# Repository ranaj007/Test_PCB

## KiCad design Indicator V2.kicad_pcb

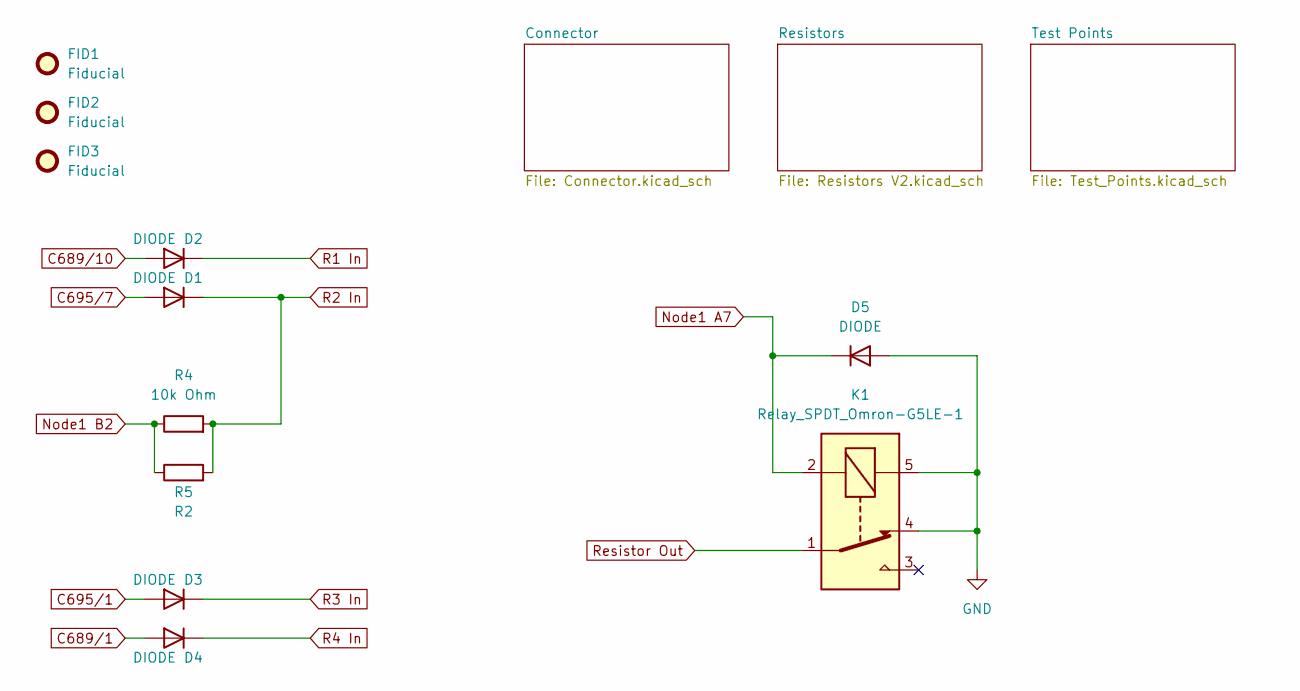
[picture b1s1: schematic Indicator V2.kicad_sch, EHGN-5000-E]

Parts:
D1, D2, D3, D4, D5: DIODE; D_SMA; MPN GS1G_R1_00001
FID1, FID2, FID3: Fiducial; Fiducial_0.5mm_Mask1.5mm
K1: Relay_SPDT_Omron-G5LE-1; MPN G5LE-14-36 DC24
R4: 10k Ohm; R_1206_3216Metric; MPN CR0805-JW-103ELF
R5: R2; R_Axial_DIN0309_L9.0mm_D3.2mm_P15.24mm_Horizontal

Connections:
C689/1: D4.2 (A); also elsewhere on the board
C689/10: D2.2 (A); also elsewhere on the board
C695/1: D3.2 (A); also elsewhere on the board
C695/7: D1.2 (A); also elsewhere on the board
GND: D5.2 (A), K1.4, K1.5; also elsewhere on the board
Node1 A7: D5.1 (K), K1.2; also elsewhere on the board
Node1 B2: R4.1, R5.1; also elsewhere on the board
R1 In: D2.1 (K); also elsewhere on the board
R2 In: D1.1 (K), R4.2, R5.2; also elsewhere on the board
R3 In: D3.1 (K); also elsewhere on the board
R4 In: D4.1 (K); also elsewhere on the board
Resistor Out: K1.1; also elsewhere on the board

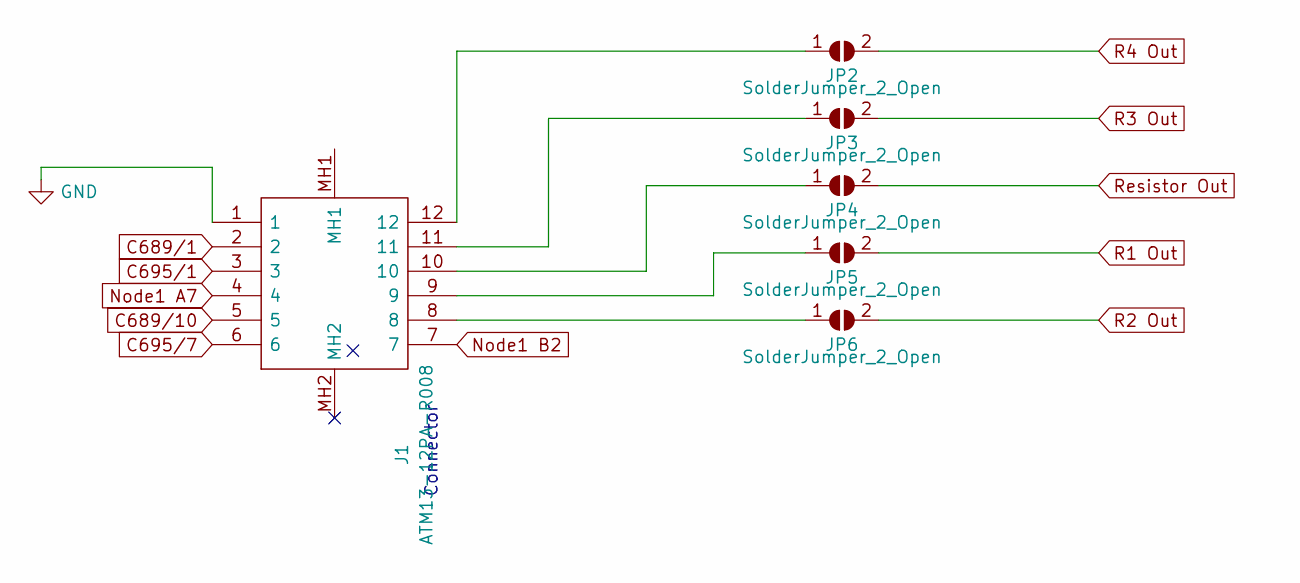
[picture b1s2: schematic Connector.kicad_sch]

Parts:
J1: ATM13-12PA-R008; ATM1312PAR008; MPN ATM13-12PA-R008
JP2, JP3, JP4, JP5, JP6: SolderJumper_2_Open; SolderJumper-2_P1.3mm_Open_Pad1.0x1.5mm

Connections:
C689/1: J1.2; also elsewhere on the board
C689/10: J1.5; also elsewhere on the board
C695/1: J1.3; also elsewhere on the board
C695/7: J1.6; also elsewhere on the board
GND: J1.1; also elsewhere on the board
unnamed: J1.8, JP6.1 (A)
unnamed: J1.9, JP5.1 (A)
unnamed: J1.10, JP4.1 (A)
unnamed: J1.11, JP3.1 (A)
unnamed: J1.12, JP2.1 (A)
Node1 A7: J1.4; also elsewhere on the board
Node1 B2: J1.7; also elsewhere on the board
R1 Out: JP5.2 (B); also elsewhere on the board
R2 Out: JP6.2 (B); also elsewhere on the board
R3 Out: JP3.2 (B); also elsewhere on the board
R4 Out: JP2.2 (B); also elsewhere on the board
Resistor Out: JP4.2 (B); also elsewhere on the board

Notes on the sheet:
Connector

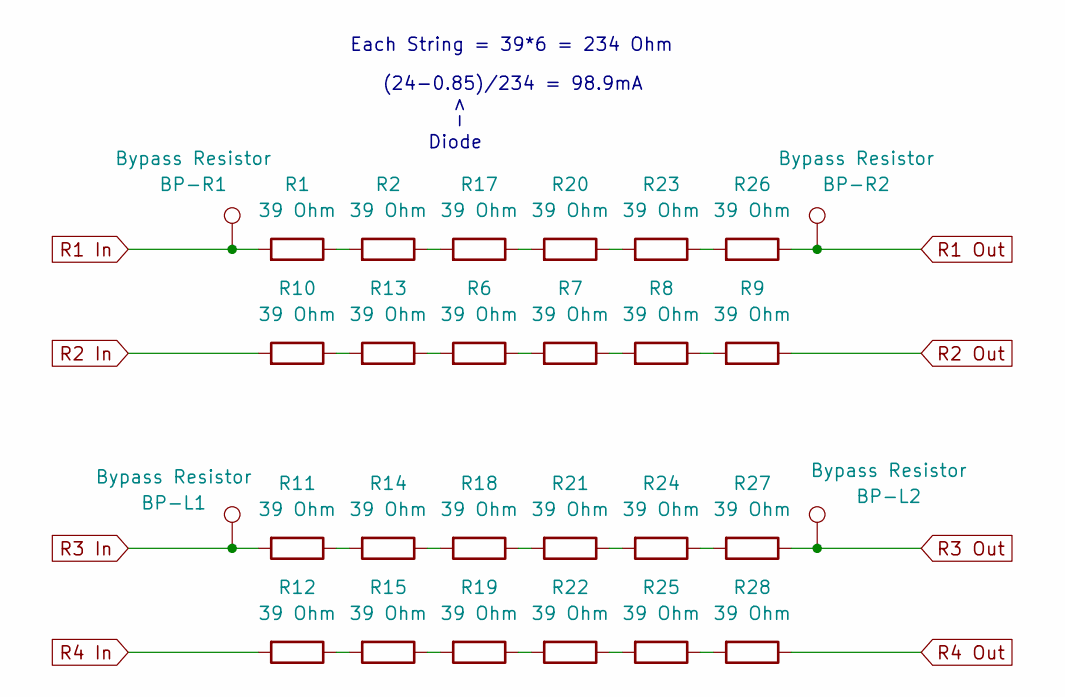
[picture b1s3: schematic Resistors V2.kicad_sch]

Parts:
BP-L1, BP-L2: Bypass Resistor; TestPoint_Keystone_5000-5004_Miniature; MPN 5002
BP-R1, BP-R2: Bypass Resistor; TestPoint_Keystone_5000-5004_Miniature; MPN 5002
R1, R2, R6, R7, R8, R9, R10, R11, R12, R13, R14, R15, R17, R18, R19, R20, R21, R22, R23, R24, R25, R26, R27, R28: 39 Ohm; R_2512_6332Metric_thermal_pad; MPN CRGP2512F15R

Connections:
unnamed: R1.1, R2.2
unnamed: R6.1, R7.2
unnamed: R7.1, R8.2
unnamed: R8.1, R9.2
unnamed: R10.1, R13.2
unnamed: R11.1, R14.2
unnamed: R12.1, R15.2
unnamed: R6.2, R13.1
unnamed: R14.1, R18.2
unnamed: R15.1, R19.2
unnamed: R17.1, R20.2
unnamed: R2.1, R17.2
unnamed: R18.1, R21.2
unnamed: R19.1, R22.2
unnamed: R20.1, R23.2
unnamed: R21.1, R24.2
unnamed: R22.1, R25.2
unnamed: R23.1, R26.2
unnamed: R24.1, R27.2
unnamed: R25.1, R28.2
R1 In: BP-R1.1, R1.2; also elsewhere on the board
R1 Out: BP-R2.1, R26.1; also elsewhere on the board
R2 In: R10.2; also elsewhere on the board
R2 Out: R9.1; also elsewhere on the board
R3 In: BP-L1.1, R11.2; also elsewhere on the board
R3 Out: BP-L2.1, R27.1; also elsewhere on the board
R4 In: R12.2; also elsewhere on the board
R4 Out: R28.1; also elsewhere on the board

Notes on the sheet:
Diode
Each String = 39*6 = 234 Ohm
(24-0.85)/234 = 98.9mA

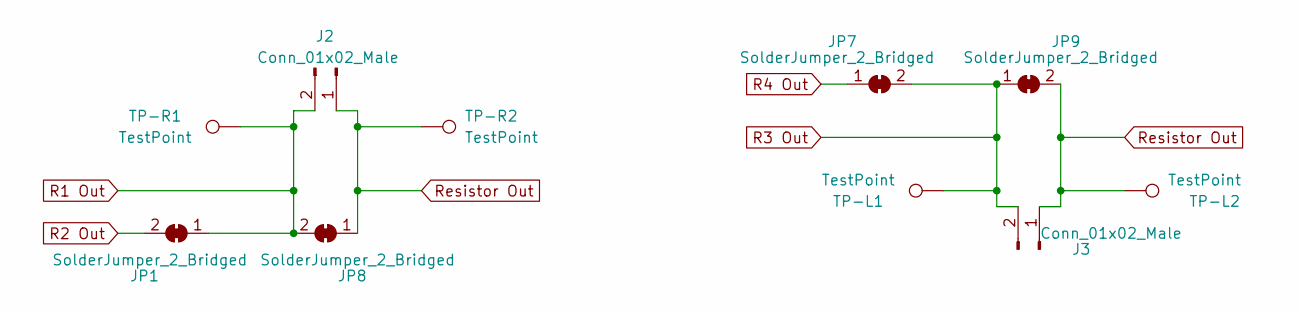
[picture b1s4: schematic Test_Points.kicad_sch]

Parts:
J2, J3: Conn_01x02_Male; PinHeader_1x02_P2.54mm_Vertical
JP1, JP7, JP8, JP9: SolderJumper_2_Bridged; SolderJumper-2_P1.3mm_Bridged_Pad1.0x1.5mm
TP-L1, TP-L2: TestPoint; TestPoint_Keystone_5000-5004_Miniature; MPN 5002
TP-R1, TP-R2: TestPoint; TestPoint_Keystone_5000-5004_Miniature; MPN 5002

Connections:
R1 Out: J2.2, JP1.1 (A), JP8.2 (B), TP-R1.1; also elsewhere on the board
R2 Out: JP1.2 (B); also elsewhere on the board
R3 Out: J3.2, JP7.2 (B), JP9.1 (A), TP-L1.1; also elsewhere on the board
R4 Out: JP7.1 (A); also elsewhere on the board
Resistor Out: J2.1, J3.1, JP8.1 (A), JP9.2 (B), TP-L2.1, TP-R2.1; also elsewhere on the board

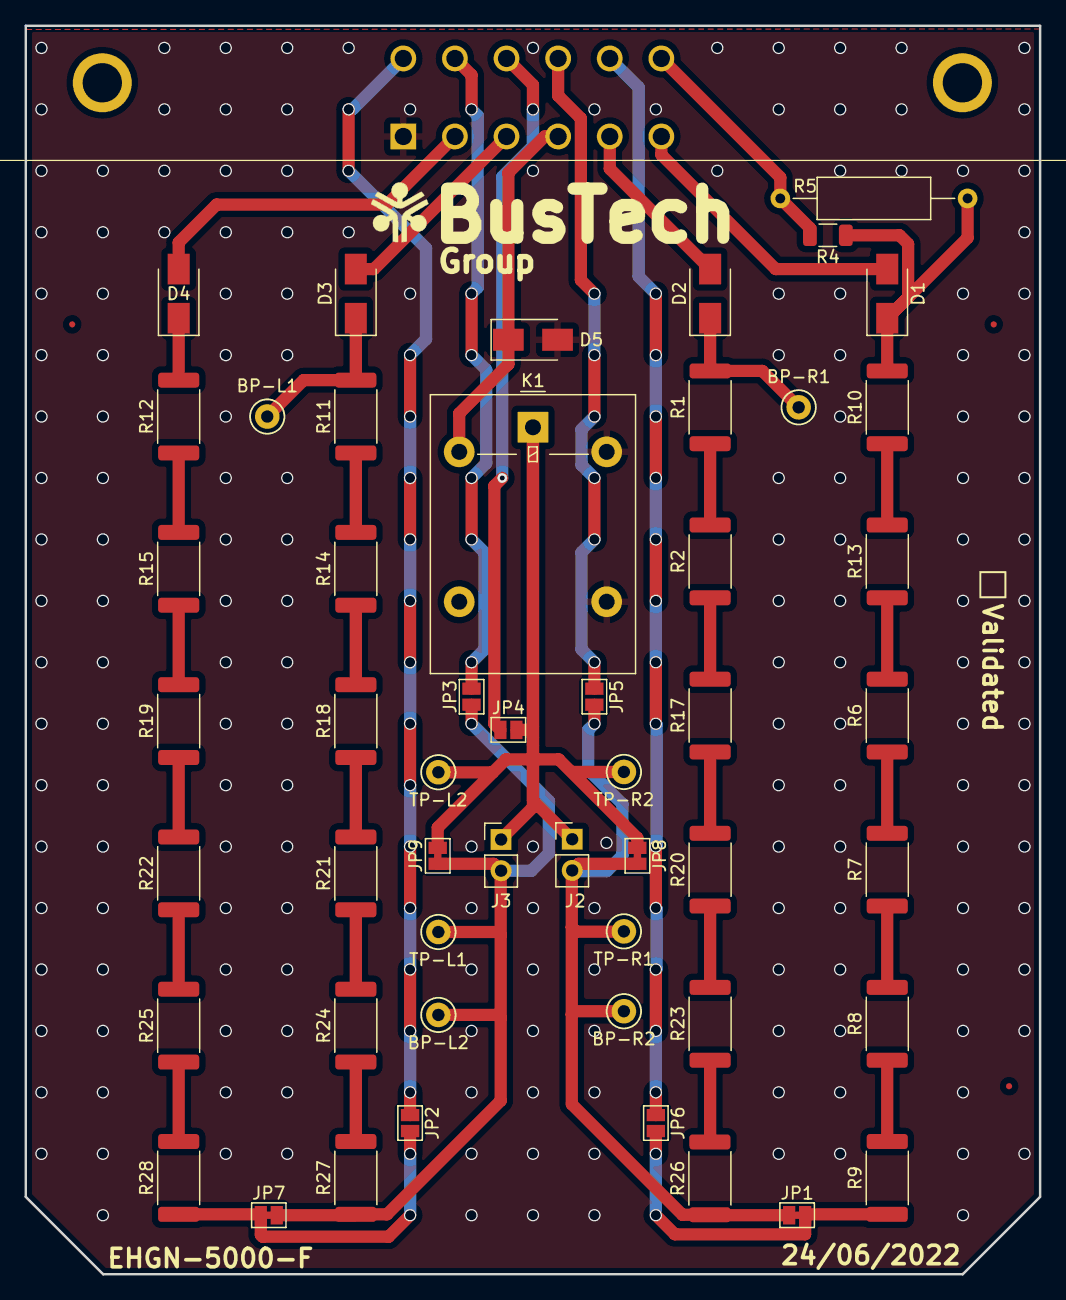
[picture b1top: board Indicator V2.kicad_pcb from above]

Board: 2 copper layers, 82.6 x 101.6 mm, 55 parts (0 on the bottom side), 41 nets.
